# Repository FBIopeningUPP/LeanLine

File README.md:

# A.T.L.A.S. - Apex Telemetry & Lap Analysis System (Project Lean Line)

A.T.L.A.S. is a bare-metal system it revolves around track-day with ur superbikes. It calculates ur lean angles, track positioning using **GPS**, and lap times at a frequency of 100Hz, it logs the data directly to your MicroSD card and visualizes the daya in custom PyQt5 Dashboard.

## The Architecture

This project is divided into 3 nodes:

### 1. The Hardware
A custom pcb designed around the **Raspberry Pi RP2040** microcontroller.
* **MCU** RP2040
* **IMU** ICM-42688-P
* **GPS** Any UART Based u-blox m10 GPS
* **STORAGE** MicroSD Card

### 2. Firmware
The firmware is purely written in C++
* Dual-Core Processing
* Ping-Pong Buffering
* Sensor Fusion Engine

### 3. The DashBoard & Simulator
A simple Desktop application built with **PyQt5** and **PyQtGraph**
* Frame Parser: it deserializes all the 32-byte into python data class
* Telemetry Plot: It renders the speed with lean angle 
* GPS Map: Renders the tracklayout based on the longitude and the latitude data.
* Lap Timer: 
* Digital Twin Simulator: A gui simulator that generates track data so u can test the dashboard physics without need physical hardware

## Bill of Materials (BoM)
A complete, itemized BOM is generated by kicad
It can be viewed: [**hardware/bom.csv**](./hardware/production/bom.csv)

## Steps To Reproduce

### Hardware

1. The parts can be sourced by providing the BoM CSV file to lcsc from where u can order the parts.
2. The [PCB](./hardware/production/pcb.zip) can be ordered through JLCPCB with a stencil for precise soldering.
3. Soldering can be done using low temp solder paste while using the stencil to create a perfect solder layer 

### Software
RP2040 bare-metal is pretty easy to program not that hard
1. Install 'arm-none-eabi-gcc' toolchain and CMake.
2. Open terminal and go into the 'firmware/'
    ``` bash
    mkdir build && cd build
    cmake -G "Ninja" -DPICO_SDK_DETCH_FROM_GIT=ON ..
    ninja

3. Through the debug pads of RP2040 the board can be programmed through the uf2 file provided in the firmware directory

### Running the Dashboard

1. Copy the telemetry.dat file from the MicroSd card
2. Install the python libraries:
    pip install PyQt5 pyqtgraph

3. Run the Digital Twin Dashboard:
    python dashboard/main.py

4. Click Load Telemetry Binary and select the MicroSd card data

# IMAGES
### Front

### Back

# USAGE OF AI
the usage of ai was done to figure out the pinout and the project structure of how everything will be done

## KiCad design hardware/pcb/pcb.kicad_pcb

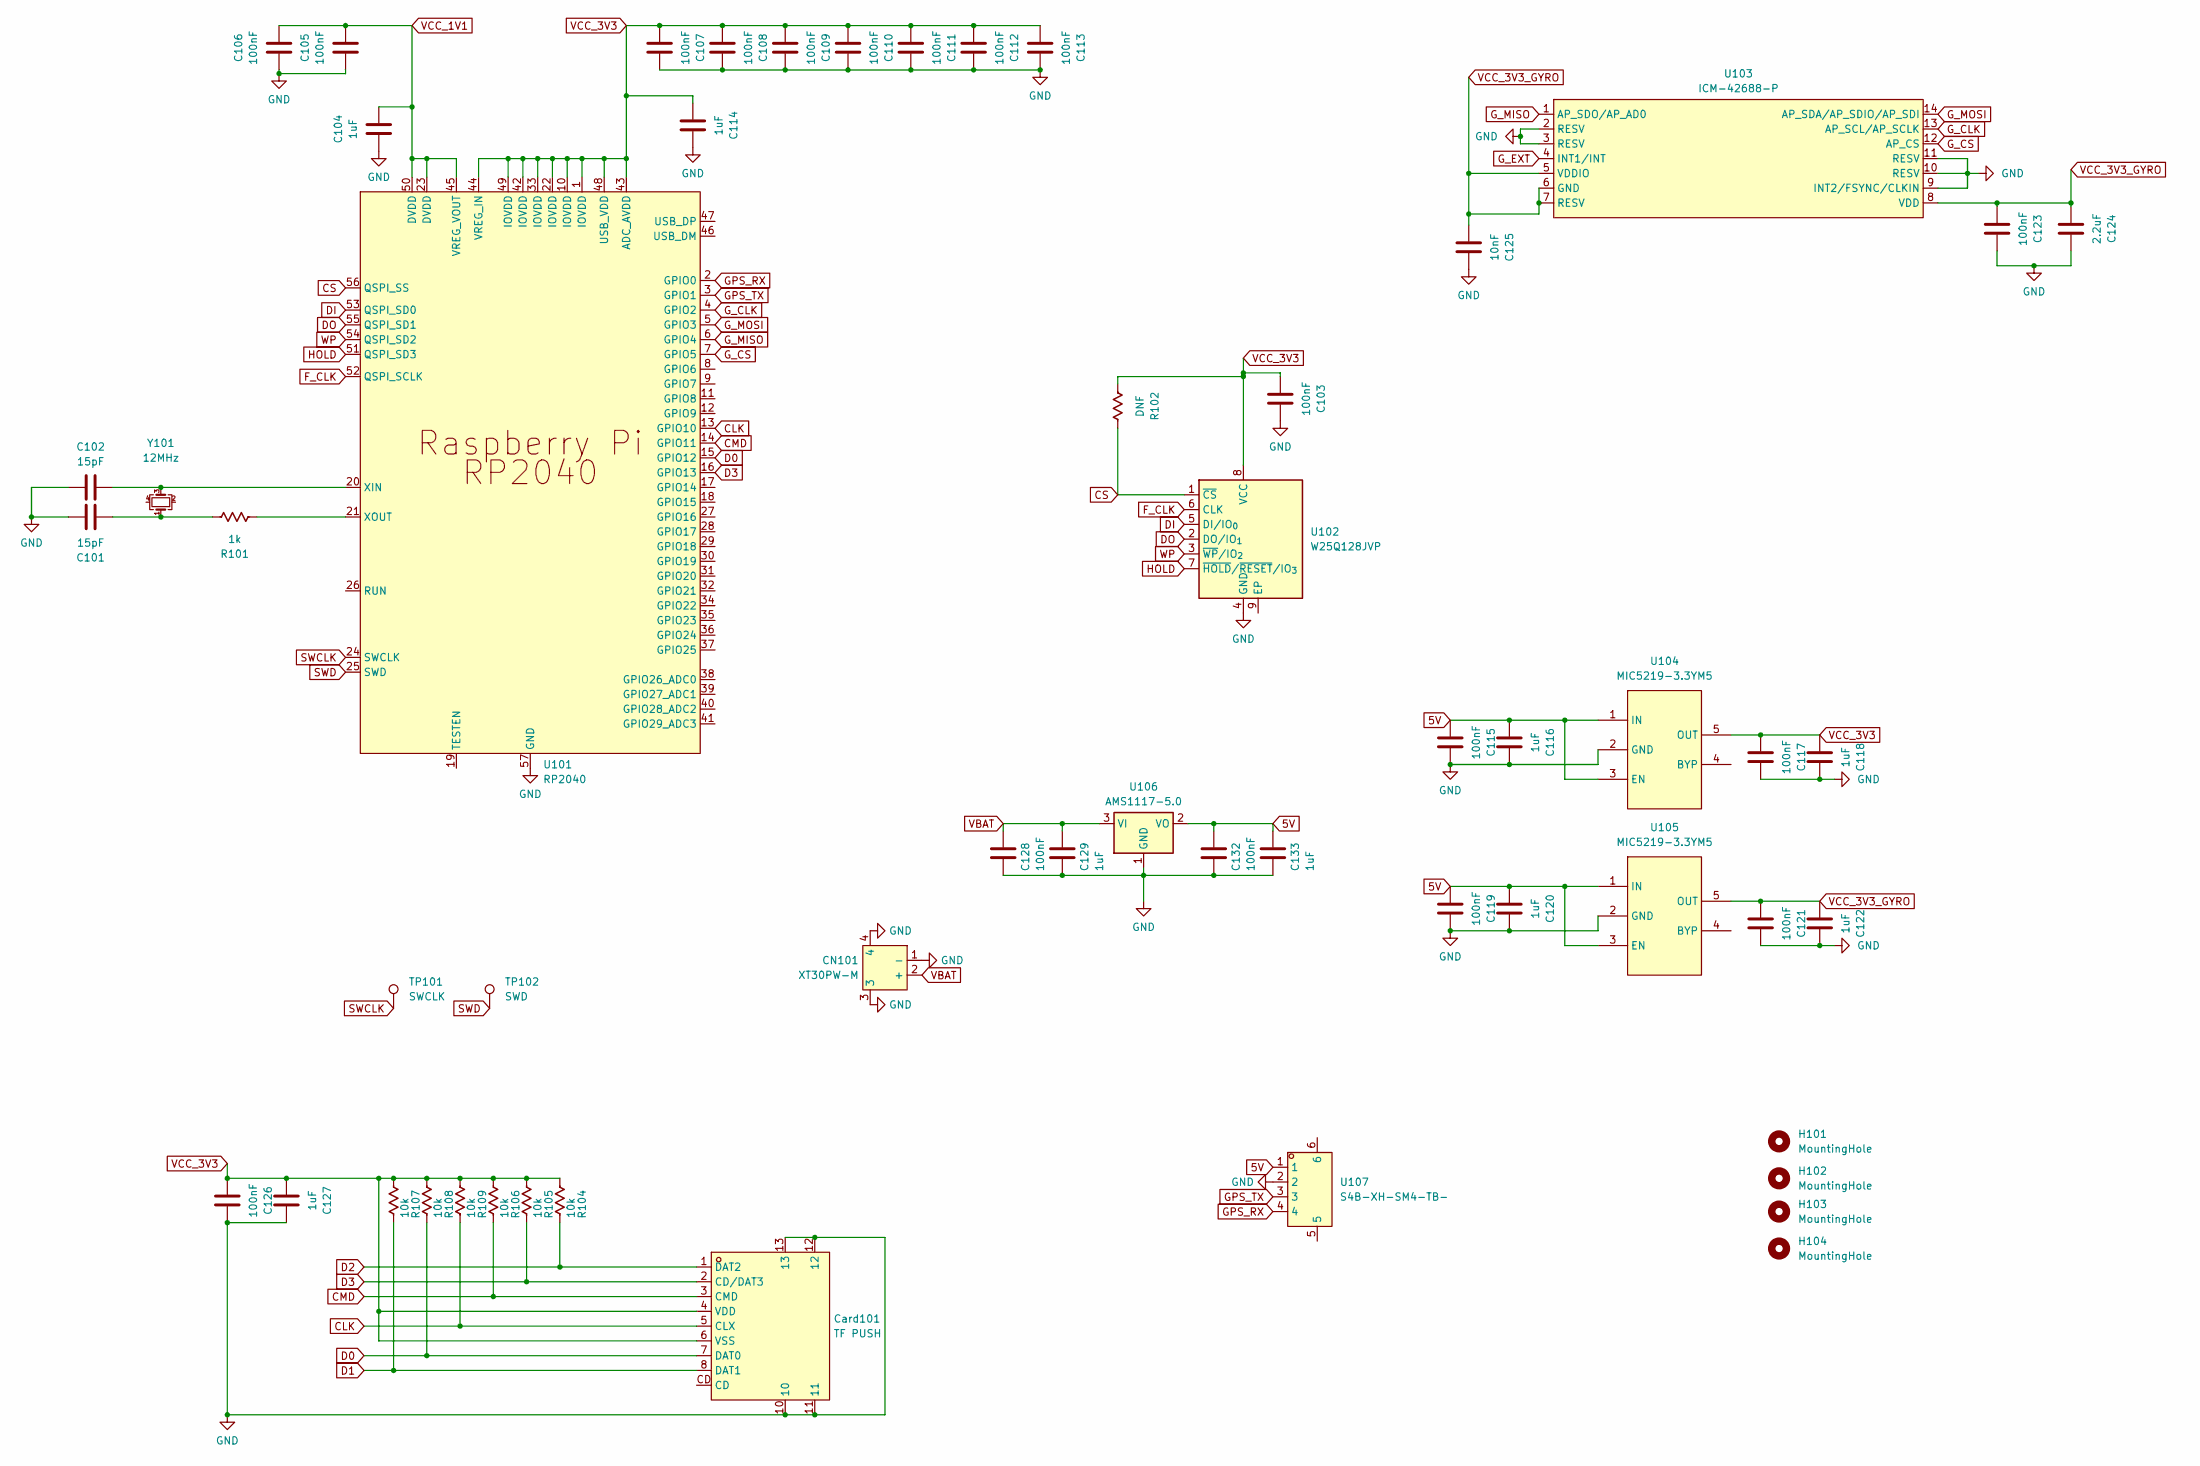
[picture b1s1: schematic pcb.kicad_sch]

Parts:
C101, C102: 15pF; C_0402_1005Metric
C103, C105, C106, C107, C108, C109, C110, C111, C112, C113, C115, C117, C119, C121, C123, C126: 100nF; C_0402_1005Metric
C104, C114, C116, C118, C120, C122, C127: 1uF; C_0402_1005Metric
C124: 2.2uF; C_0402_1005Metric
C125: 10nF; C_0402_1005Metric
C128, C132: 100nF; C_0603_1608Metric
C129, C133: 1uF; C_0603_1608Metric
CN101: XT30PW-M; CONN-TH_XT30PW-M; LCSC Part C431092
Card101: TF PUSH; TF-SMD_TF-PUSH; MPN TF PUSH; LCSC Part C393941
H101, H102, H103, H104: MountingHole; MountingHole_3.2mm_M3_DIN965
R101: 1k; R_0402_1005Metric
R102: DNF; R_0402_1005Metric
R104, R105, R106, R107, R108, R109: 10k; R_0402_1005Metric
TP101: SWCLK; TestPoint_Pad_D1.0mm
TP102: SWD; TestPoint_Pad_D1.0mm
U101: RP2040; LQFN-56_L7.0-W7.0-P0.4-EP; MPN RP2040; LCSC Part C2040
U102: W25Q128JVP; WSON-8-1EP_6x5mm_P1.27mm_EP3.4x4.3mm
U103: ICM-42688-P; LGA-14_L3.0-W2.5-P0.50-TL; LCSC Part C1850418
U104, U105: MIC5219-3.3YM5; SOT-23-5; LCSC Part C29613
U106: AMS1117-5.0; SOT-223-3_TabPin2
U107: S4B-XH-SM4-TB-; CONN-SMD_S4B-XH-SM4-TB-LF-SN; MPN S4B-XH-SM4-TB(LF)(SN); LCSC Part C161861
Y101: 12MHz; Crystal_SMD_3225-4Pin_3.2x2.5mm

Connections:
5V: C115.1, C116.1, C119.1, C120.1, C132.1, C133.1, U104.1 (IN), U104.3 (EN), U105.1 (IN), U105.3 (EN), U106.2 (VO), U107.1
CLK: Card101.5 (CLX), R109.1, U101.13 (GPIO10)
CMD: Card101.3 (CMD), R106.1, U101.14 (GPIO11)
CS: R102.1, U101.56 (QSPI_SS), U102.1 (~CS)
D0: Card101.7 (DAT0), R108.1, U101.15 (GPIO12)
D1: Card101.8 (DAT1), R107.1
D2: Card101.1 (DAT2), R104.1
D3: Card101.2 (CD/DAT3), R105.1, U101.16 (GPIO13)
DI: U101.53 (QSPI_SD0), U102.5 (DI/IO_{0})
DO: U101.55 (QSPI_SD1), U102.2 (DO/IO_{1})
F_CLK: U101.52 (QSPI_SCLK), U102.6 (CLK)
GND: C101.1, C102.1, C103.2, C104.1, C105.1, C106.1, C107.2, C108.2, C109.2, C110.2, C111.2, C112.2, C113.2, C114.2, C115.2, C116.2, C117.2, C118.2, C119.2, C120.2, C121.2, C122.2, C123.2, C124.2, C125.2, C126.2, C127.2, C128.2, C129.2, C132.2, C133.2, CN101.1 (-), CN101.3, CN101.4, Card101.10, Card101.11, Card101.12, Card101.13, U101.57 (GND), U102.4 (GND), U103.2 (RESV), U103.3 (RESV), U103.9 (INT2/FSYNC/CLKIN), U103.10 (RESV), U103.11 (RESV), U104.2 (GND), U105.2 (GND), U106.1 (GND), U107.2
GPS_RX: U101.2 (GPIO0), U107.4
GPS_TX: U101.3 (GPIO1), U107.3
G_CLK: U101.4 (GPIO2), U103.13 (AP_SCL/AP_SCLK)
G_CS: U101.7 (GPIO5), U103.12 (AP_CS)
G_EXT: U103.4 (INT1/INT)
G_MISO: U101.6 (GPIO4), U103.1 (AP_SDO/AP_AD0)
G_MOSI: U101.5 (GPIO3), U103.14 (AP_SDA/AP_SDIO/AP_SDI)
HOLD: U101.51 (QSPI_SD3), U102.7 (~HOLD/~RESET/IO_{3})
unnamed: C101.2, R101.1, Y101.1
unnamed: C102.2, U101.20 (XIN), Y101.3
unnamed: R101.2, U101.21 (XOUT)
SWCLK: TP101.1, U101.24 (SWCLK)
SWD: TP102.1, U101.25 (SWD)
VBAT: C128.1, C129.1, CN101.2 (+), U106.3 (VI)
VCC_1V1: C104.2, C105.2, C106.2, U101.23 (DVDD), U101.45 (VREG_VOUT), U101.50 (DVDD)
VCC_3V3: C103.1, C107.1, C108.1, C109.1, C110.1, C111.1, C112.1, C113.1, C114.1, C117.1, C118.1, C126.1, C127.1, Card101.4 (VDD), Card101.6 (VSS), R102.2, R104.2, R105.2, R106.2, R107.2, R108.2, R109.2, U101.1 (IOVDD), U101.10 (IOVDD), U101.22 (IOVDD), U101.33 (IOVDD), U101.42 (IOVDD), U101.43 (ADC_AVDD), U101.44 (VREG_IN), U101.48 (USB_VDD), U101.49 (IOVDD), U102.8 (VCC), U104.5 (OUT)
VCC_3V3_GYRO: C121.1, C122.1, C123.1, C124.1, C125.1, U103.5 (VDDIO), U103.6 (GND), U103.7 (RESV), U103.8 (VDD), U105.5 (OUT)
WP: U101.54 (QSPI_SD2), U102.3 (~WP/IO_{2})

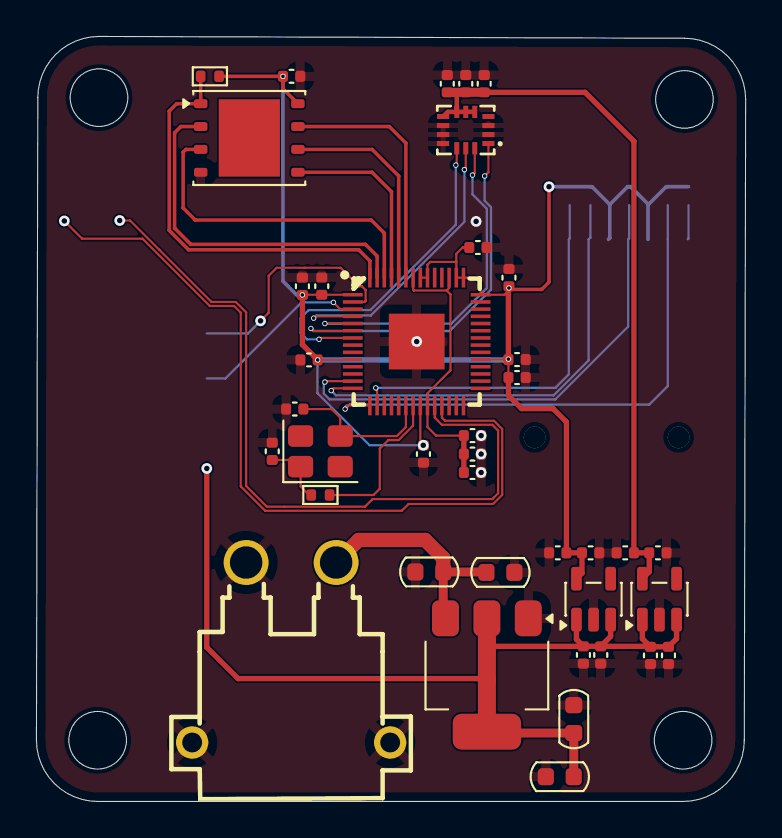
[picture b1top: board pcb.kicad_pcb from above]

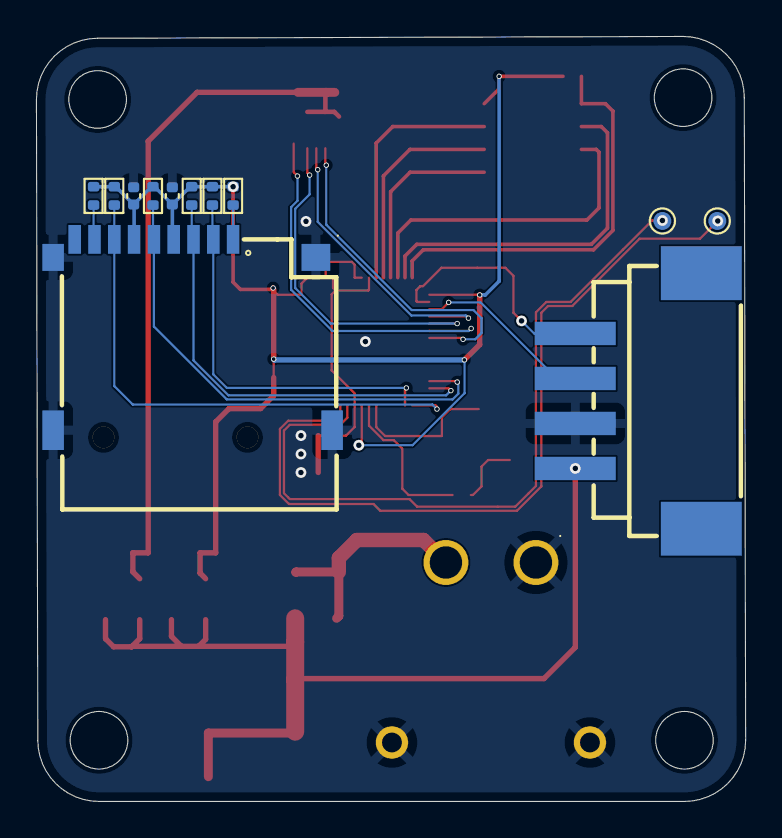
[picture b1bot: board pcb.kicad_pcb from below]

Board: 2 copper layers, 39.4 x 42.5 mm, 55 parts (12 on the bottom side), 29 nets.

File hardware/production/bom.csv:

Designator,Footprint,Quantity,Value,LCSC Part #
"C101, C102",0402,2,15pF,
"C103, C105, C106, C107, C108, C109, C110, C111, C112, C113, C115, C117, C119, C121, C123, C126",0402,16,100nF,
"C104, C114, C116, C118, C120, C122, C127",0402,7,1uF,
C124,0402,1,2.2uF,
C125,0402,1,10nF,
"C128, C132",0603,2,100nF,
"C129, C133",0603,2,1uF,
CARD101,TF-SMD_TF-PUSH,1,TF PUSH,C393941
CN101,CONN-TH_XT30PW-M,1,XT30PW-M,C431092
R101,0402,1,1k,
R102,0402,1,DNF,
"R104, R105, R106, R107, R108, R109",0402,6,10k,
U101,LQFN-56_L7.0-W7.0-P0.4-EP,1,RP2040,C2040
U102,WSON-8-1EP_6x5mm_P1.27mm_EP3.4x4.3mm,1,W25Q128JVP,
U103,LGA-14_L3.0-W2.5-P0.50-TL,1,ICM-42688-P,C1850418
"U104, U105",SOT-23-5,2,MIC5219-3.3YM5,C29613
U106,SOT-223-3_TabPin2,1,AMS1117-5.0,
U107,CONN-SMD_S4B-XH-SM4-TB-LF-SN,1,S4B-XH-SM4-TB-,C161861
Y101,Crystal_SMD_3225-4Pin_3.2x2.5mm,1,12MHz,
